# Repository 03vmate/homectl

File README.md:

# homectl
Common software and hardware platform for a home automation system

## homectl-hw
KiCAD project for hardware platform.
Utilizes a Pi Pico, and two stepper motor controller modules(TMC2208 or compatible and a DRV8825/A4988 or compatible).
PCB layout optimized for DIY home PCB milling

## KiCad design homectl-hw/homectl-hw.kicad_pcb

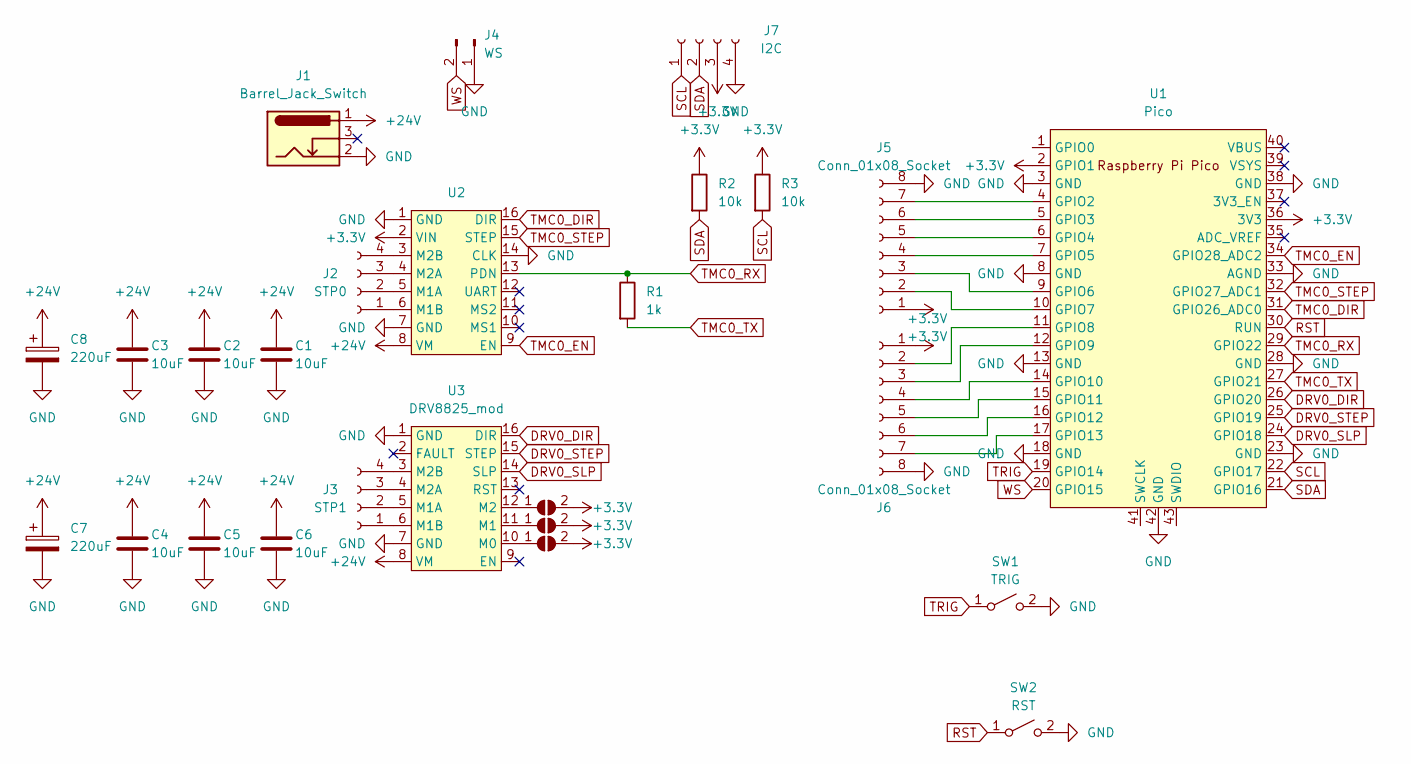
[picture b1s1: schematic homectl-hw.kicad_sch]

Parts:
C1, C2, C3, C4, C5, C6: 10uF; C_0805_2012Metric_Pad1.18x1.45mm_HandSolder
C7, C8: 220uF; CP_Radial_D8.0mm_P3.50mm
J1: Barrel_Jack_Switch; BarrelJack_Horizontal
J2: STP0; JST_XH_B4B-XH-A_1x04_P2.50mm_Vertical
J3: STP1; JST_XH_B4B-XH-A_1x04_P2.50mm_Vertical
J4: WS; JST_PH_B2B-PH-K_1x02_P2.00mm_Vertical
J5, J6: Conn_01x08_Socket; JST_PH_B8B-PH-K_1x08_P2.00mm_Vertical
J7: I2C; JST_XH_B4B-XH-A_1x04_P2.50mm_Vertical
JP1, JP2, JP3: M2; SolderJumper-2_P1.3mm_Open_Pad1.0x1.5mm
R1: 1k; R_0805_2012Metric_Pad1.20x1.40mm_HandSolder
R2, R3: 10k; R_0805_2012Metric_Pad1.20x1.40mm_HandSolder
SW1: TRIG; SW_Cherry_MX_1.00u_Plate
SW2: RST; SW_PUSH_6mm
U1: Pico; RPi_Pico_SMD_TH
U2: StepperModule
U3: DRV8825_mod; StepperModule

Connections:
+3.3V: J5.1, J6.1, J7.3, JP1.2 (B), JP2.2 (B), JP3.2 (B), R2.1, R3.1, U1.2 (GPIO1), U1.36 (3V3), U2.2 (VIN)
+24V: C1.1, C2.1, C3.1, C4.1, C5.1, C6.1, C7.1, C8.1, J1.1, U2.8 (VM), U3.8 (VM)
DRV0_DIR: U1.26 (GPIO20), U3.16 (DIR)
DRV0_SLP: U1.24 (GPIO18), U3.14 (SLP)
DRV0_STEP: U1.25 (GPIO19), U3.15 (STEP)
GND: C1.2, C2.2, C3.2, C4.2, C5.2, C6.2, C7.2, C8.2, J1.2, J4.1, J5.8, J6.8, J7.4, SW1.2 (B), SW2.2 (B), U1.3 (GND), U1.8 (GND), U1.13 (GND), U1.18 (GND), U1.23 (GND), U1.28 (GND), U1.33 (AGND), U1.38 (GND), U1.42 (GND), U2.1 (GND), U2.7 (GND), U2.14 (CLK), U3.1 (GND), U3.7 (GND)
unnamed: J2.1, U2.6 (M1B)
unnamed: J2.2, U2.5 (M1A)
unnamed: J2.3, U2.4 (M2A)
unnamed: J2.4, U2.3 (M2B)
unnamed: J3.1, U3.6 (M1B)
unnamed: J3.2, U3.5 (M1A)
unnamed: J3.3, U3.4 (M2A)
unnamed: J3.4, U3.3 (M2B)
unnamed: J5.2, U1.10 (GPIO7)
unnamed: J5.3, U1.9 (GPIO6)
unnamed: J5.4, U1.7 (GPIO5)
unnamed: J5.5, U1.6 (GPIO4)
unnamed: J5.6, U1.5 (GPIO3)
unnamed: J5.7, U1.4 (GPIO2)
unnamed: J6.2, U1.11 (GPIO8)
unnamed: J6.3, U1.12 (GPIO9)
unnamed: J6.4, U1.14 (GPIO10)
unnamed: J6.5, U1.15 (GPIO11)
unnamed: J6.6, U1.16 (GPIO12)
unnamed: J6.7, U1.17 (GPIO13)
unnamed: JP1.1 (A), U3.12 (M2)
unnamed: JP2.1 (A), U3.11 (M1)
unnamed: JP3.1 (A), U3.10 (M0)
RST: SW2.1 (A), U1.30 (RUN)
SCL: J7.1, R3.2, U1.22 (GPIO17)
SDA: J7.2, R2.2, U1.21 (GPIO16)
TMC0_DIR: U1.31 (GPIO26_ADC0), U2.16 (DIR)
TMC0_EN: U1.34 (GPIO28_ADC2), U2.9 (EN)
TMC0_RX: R1.1, U1.29 (GPIO22), U2.13 (PDN)
TMC0_STEP: U1.32 (GPIO27_ADC1), U2.15 (STEP)
TMC0_TX: R1.2, U1.27 (GPIO21)
TRIG: SW1.1 (A), U1.19 (GPIO14)
WS: J4.2, U1.20 (GPIO15)

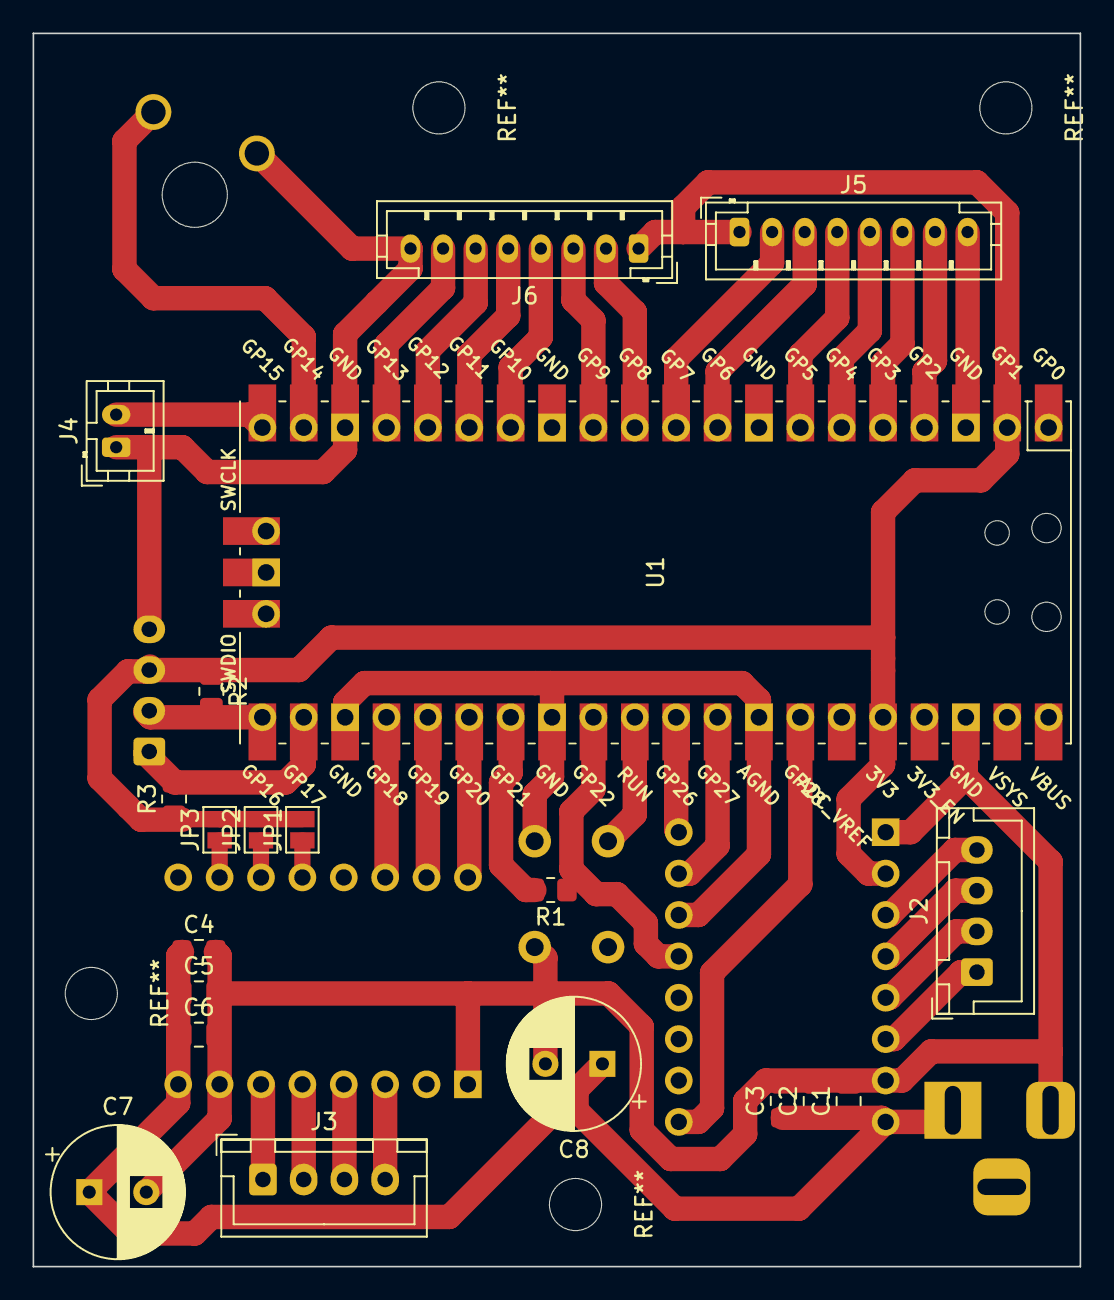
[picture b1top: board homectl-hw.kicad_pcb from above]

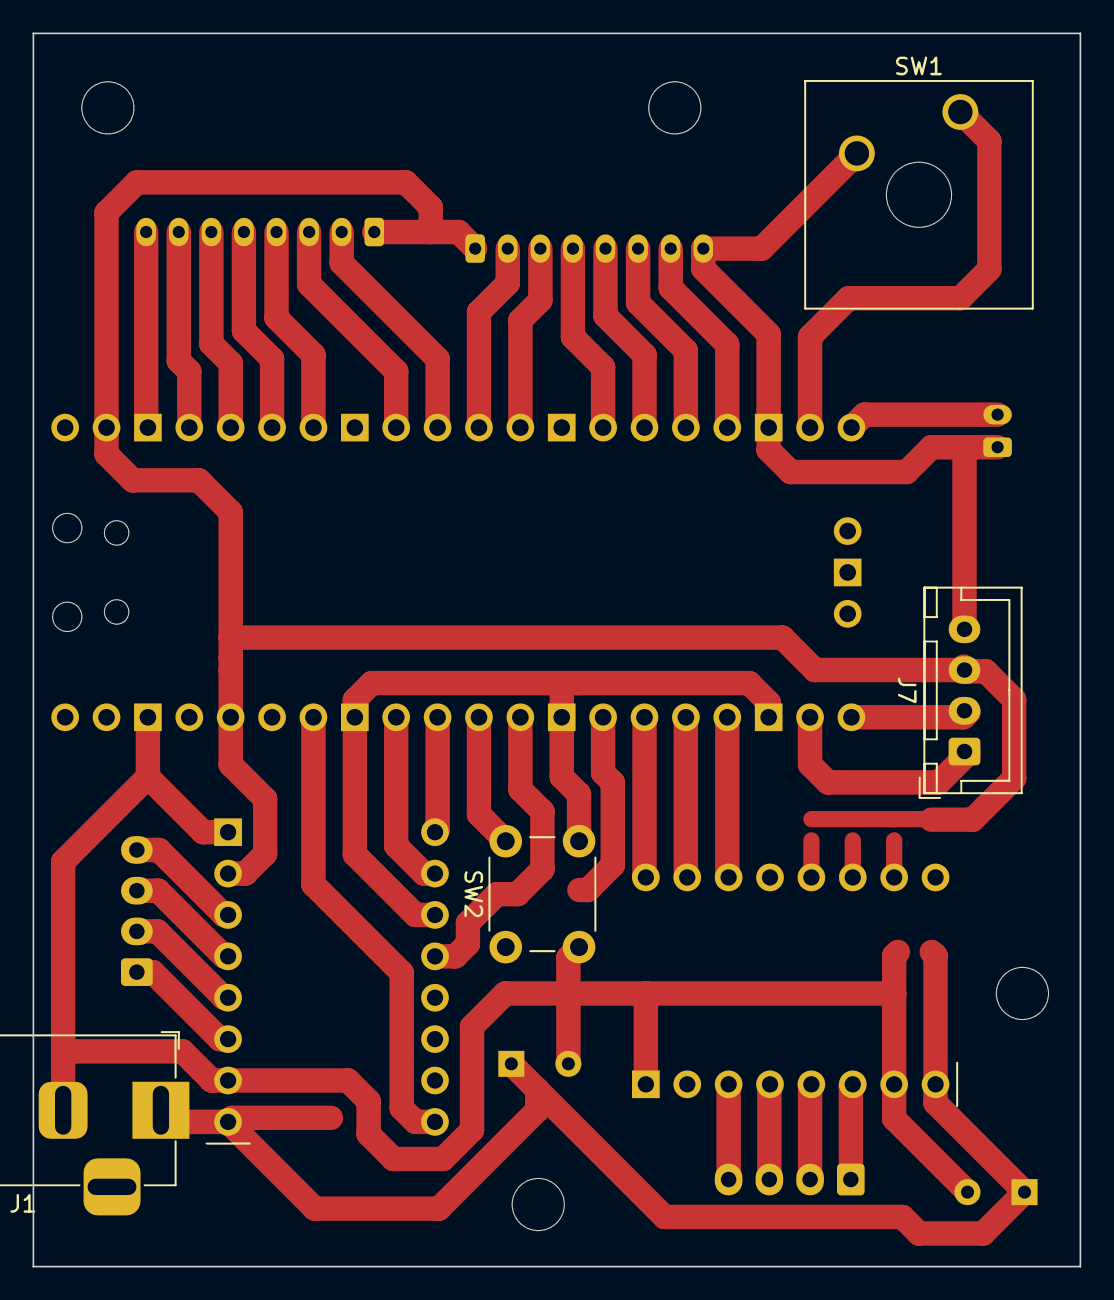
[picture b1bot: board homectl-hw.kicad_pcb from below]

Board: 2 copper layers, 64.3 x 75.7 mm, 26 parts (6 on the bottom side), 39 nets.

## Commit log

2024-01-05 Add KiCAD project
2024-01-05 Update readme with hardware
